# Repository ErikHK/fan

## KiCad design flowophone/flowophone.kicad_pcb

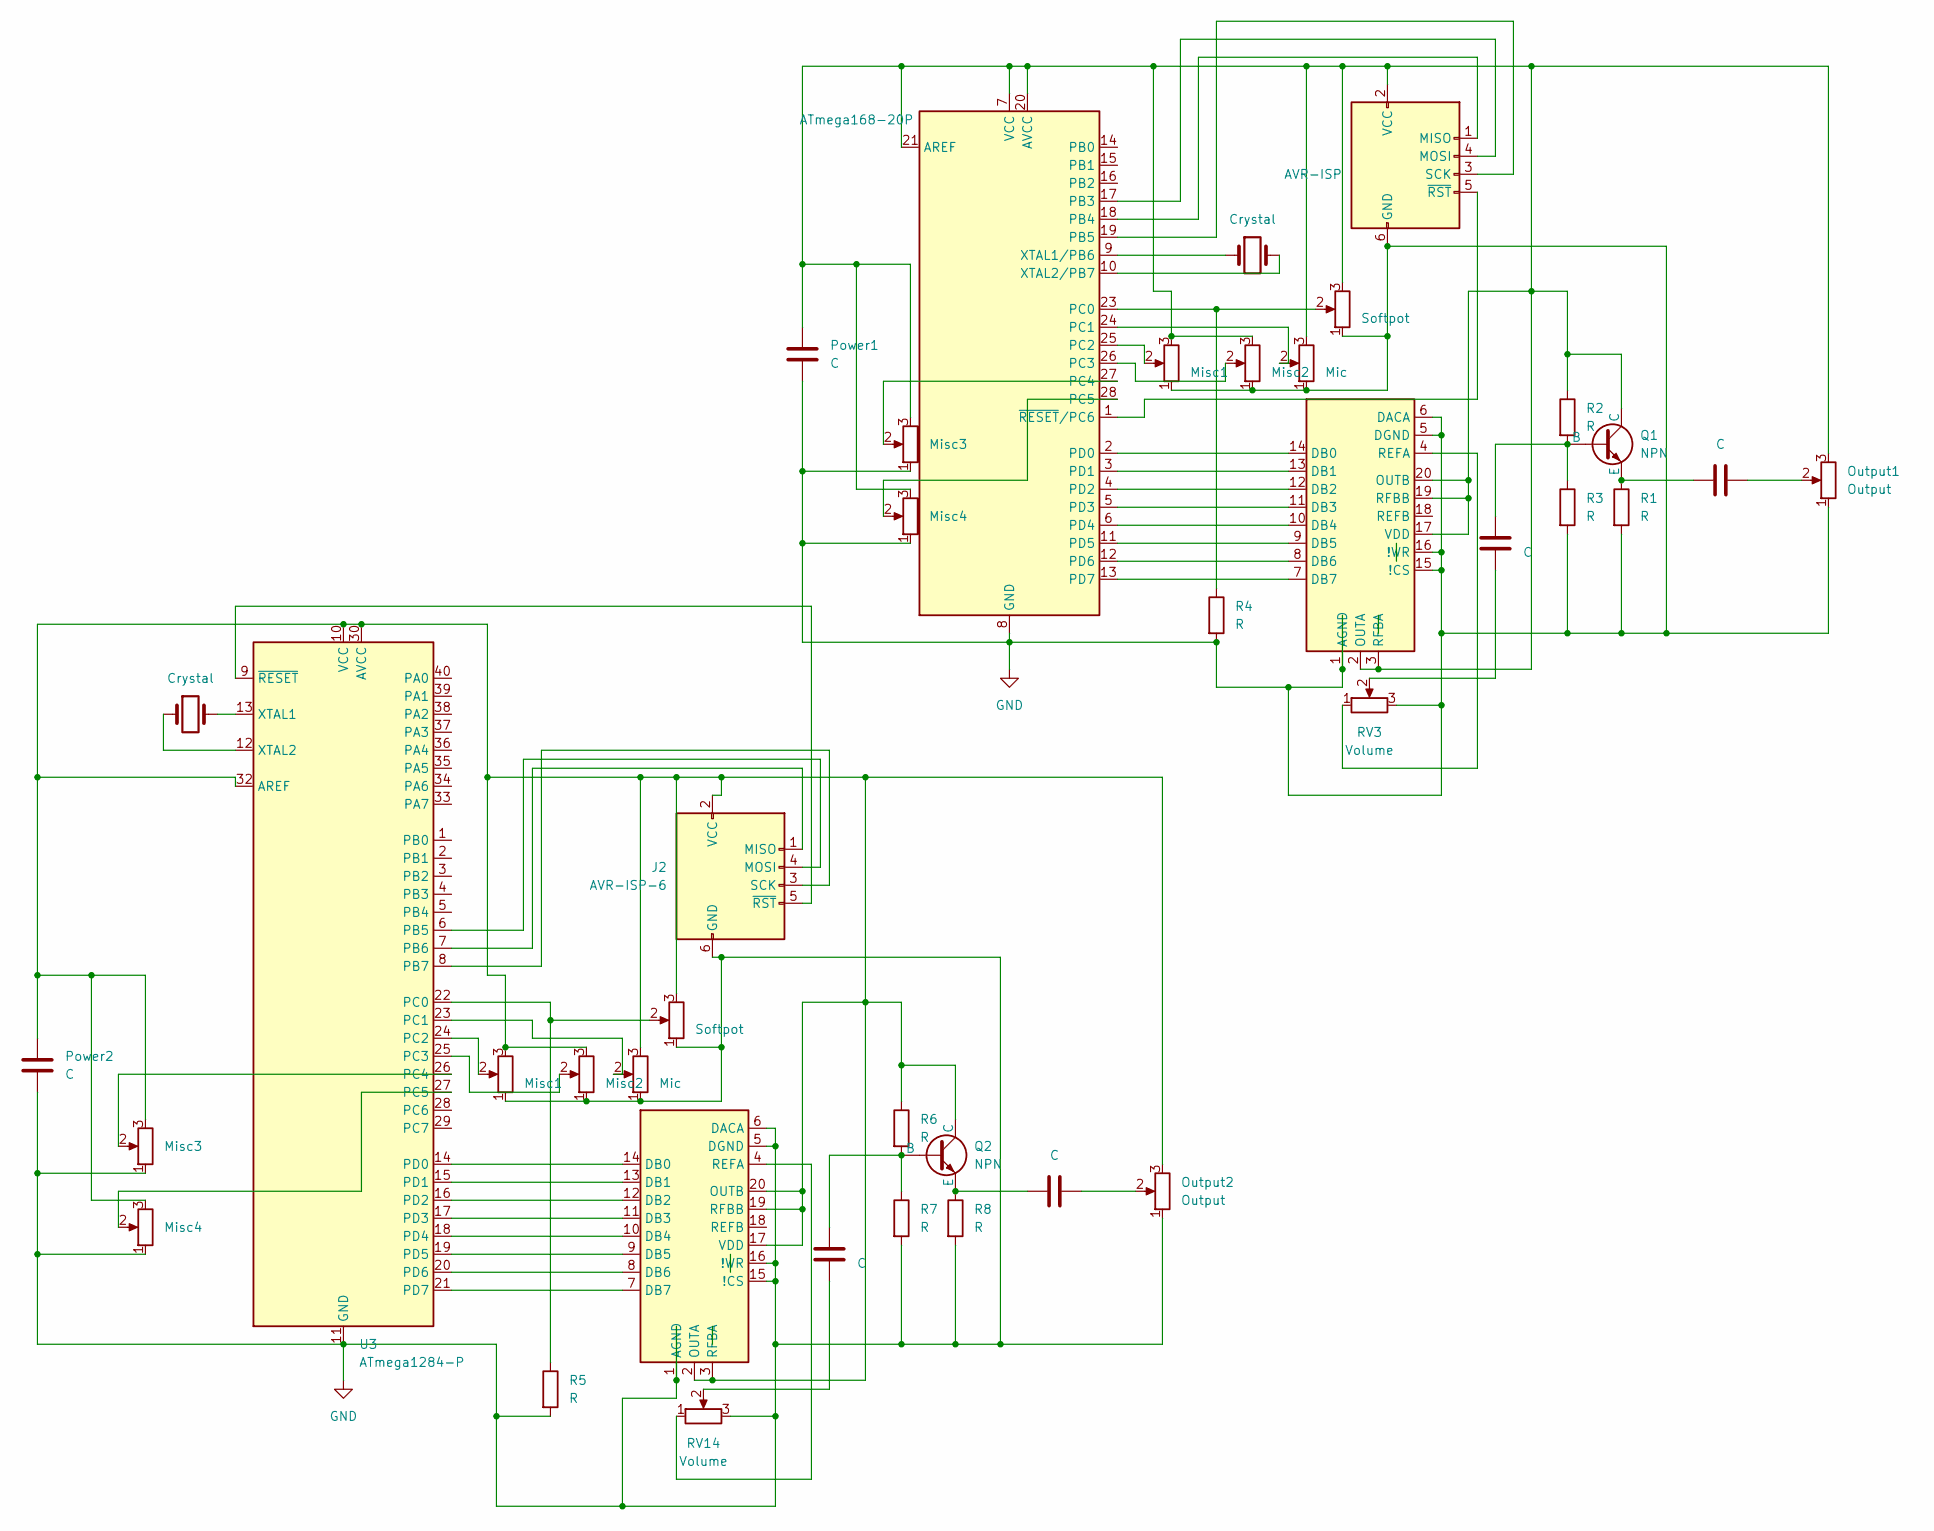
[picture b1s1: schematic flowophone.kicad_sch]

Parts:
C1, C2, C3, C4: C; PinHeader_1x02_P2.54mm_Vertical
J1: AVR-ISP; PinHeader_2x03_P2.54mm_Vertical
J2: AVR-ISP-6; PinHeader_2x03_P2.54mm_Vertical
Output1, Output2: Output; PinHeader_1x03_P2.54mm_Vertical
Power1, Power2: C; PinHeader_1x02_P2.54mm_Vertical
Q1, Q2: NPN; PinHeader_1x03_P2.54mm_Vertical
R1, R2, R3, R4, R5, R6, R7, R8: R; PinHeader_1x02_P2.54mm_Vertical
RV1, RV13: Softpot; PinHeader_1x03_P2.54mm_Vertical
RV2, RV12: Mic; PinHeader_1x03_P2.54mm_Vertical
RV3, RV14: Volume; PinHeader_1x03_P2.54mm_Vertical
RV4, RV10: Misc1; PinHeader_1x03_P2.54mm_Vertical
RV5, RV11: Misc2; PinHeader_1x03_P2.54mm_Vertical
RV6, RV8: Misc3; PinHeader_1x03_P2.54mm_Vertical
RV7, RV9: Misc4; PinHeader_1x03_P2.54mm_Vertical
U1: ATmega168-20P; DIP-28_W7.62mm
U2, U4: DIP-20_W7.62mm
U3: ATmega1284-P; DIP-40_W15.24mm
Y1, Y2: Crystal; PinHeader_1x02_P2.54mm_Vertical

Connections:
GND: J1.6 (GND), J2.6 (GND), Output1.1, Output2.1, Power1.1, Power2.1, R1.2, R3.2, R4.2, R5.2, R7.2, R8.2, RV1.1, RV2.1, RV3.3, RV4.1, RV5.1, RV6.1, RV7.1, RV8.1, RV9.1, RV10.1, RV11.1, RV12.1, RV13.1, RV14.3, U1.8 (GND), U1.22 (GND), U2.1 (AGND), U2.5 (DGND), U2.6 (DACA), U2.15 (!CS), U2.16 (!WR), U3.11 (GND), U3.31 (GND), U4.1 (AGND), U4.5 (DGND), U4.6 (DACA), U4.15 (!CS), U4.16 (!WR)
unnamed: C1.2, RV3.2
unnamed: C2.2, Output1.2
unnamed: C3.2, RV14.2
unnamed: C4.2, Output2.2
unnamed: J1.1 (MISO), U1.18 (PB4)
unnamed: J1.4 (MOSI), U1.17 (PB3)
unnamed: J1.3 (SCK), U1.19 (PB5)
unnamed: J1.2 (VCC), Output1.3, Power1.2, Q1.1 (C), R2.1, RV1.3, RV2.3, RV4.3, RV5.3, RV6.3, RV7.3, U1.7 (VCC), U1.20 (AVCC), U1.21 (AREF), U2.2 (OUTA), U2.3 (RFBA), U2.17 (VDD), U2.19 (RFBB), U2.20 (OUTB)
unnamed: J1.5 (~RST), U1.1 (~RESET/PC6)
unnamed: J2.1 (MISO), U3.7 (PB6)
unnamed: J2.4 (MOSI), U3.6 (PB5)
unnamed: J2.3 (SCK), U3.8 (PB7)
unnamed: J2.2 (VCC), Output2.3, Power2.2, Q2.1 (C), R6.1, RV8.3, RV9.3, RV10.3, RV11.3, RV12.3, RV13.3, U3.10 (VCC), U3.30 (AVCC), U3.32 (AREF), U4.2 (OUTA), U4.3 (RFBA), U4.17 (VDD), U4.19 (RFBB), U4.20 (OUTB)
unnamed: J2.5 (~RST), U3.9 (~RESET)
unnamed: C1.1, Q1.2 (B), R2.2, R3.1
unnamed: C2.1, Q1.3 (E), R1.1
unnamed: C3.1, Q2.2 (B), R6.2, R7.1
unnamed: C4.1, Q2.3 (E), R8.1
unnamed: R4.1, RV1.2, U1.23 (PC0)
unnamed: RV2.2, U1.24 (PC1)
unnamed: RV4.2, U1.25 (PC2)
unnamed: RV5.2, U1.26 (PC3)
unnamed: RV6.2, U1.27 (PC4)
unnamed: RV7.2, U1.28 (PC5)
unnamed: U1.2 (PD0), U2.14 (DB0)
unnamed: U1.3 (PD1), U2.13 (DB1)
unnamed: U1.4 (PD2), U2.12 (DB2)
unnamed: U1.5 (PD3), U2.11 (DB3)
unnamed: U1.6 (PD4), U2.10 (DB4)
unnamed: U1.11 (PD5), U2.9 (DB5)
unnamed: U1.12 (PD6), U2.8 (DB6)
unnamed: U1.13 (PD7), U2.7 (DB7)
unnamed: U1.9 (XTAL1/PB6), Y1.1
unnamed: U1.10 (XTAL2/PB7), Y1.2
unnamed: RV3.1, U2.4 (REFA)
unnamed: R5.1, RV13.2, U3.22 (PC0)
unnamed: RV12.2, U3.23 (PC1)
unnamed: RV10.2, U3.24 (PC2)
unnamed: RV11.2, U3.25 (PC3)
unnamed: RV8.2, U3.26 (PC4)
unnamed: RV9.2, U3.27 (PC5)
unnamed: U3.14 (PD0), U4.14 (DB0)
unnamed: U3.15 (PD1), U4.13 (DB1)
unnamed: U3.16 (PD2), U4.12 (DB2)
unnamed: U3.17 (PD3), U4.11 (DB3)
unnamed: U3.18 (PD4), U4.10 (DB4)
unnamed: U3.19 (PD5), U4.9 (DB5)
unnamed: U3.20 (PD6), U4.8 (DB6)
unnamed: U3.21 (PD7), U4.7 (DB7)
unnamed: U3.13 (XTAL1), Y2.2
unnamed: U3.12 (XTAL2), Y2.1
unnamed: RV14.1, U4.4 (REFA)

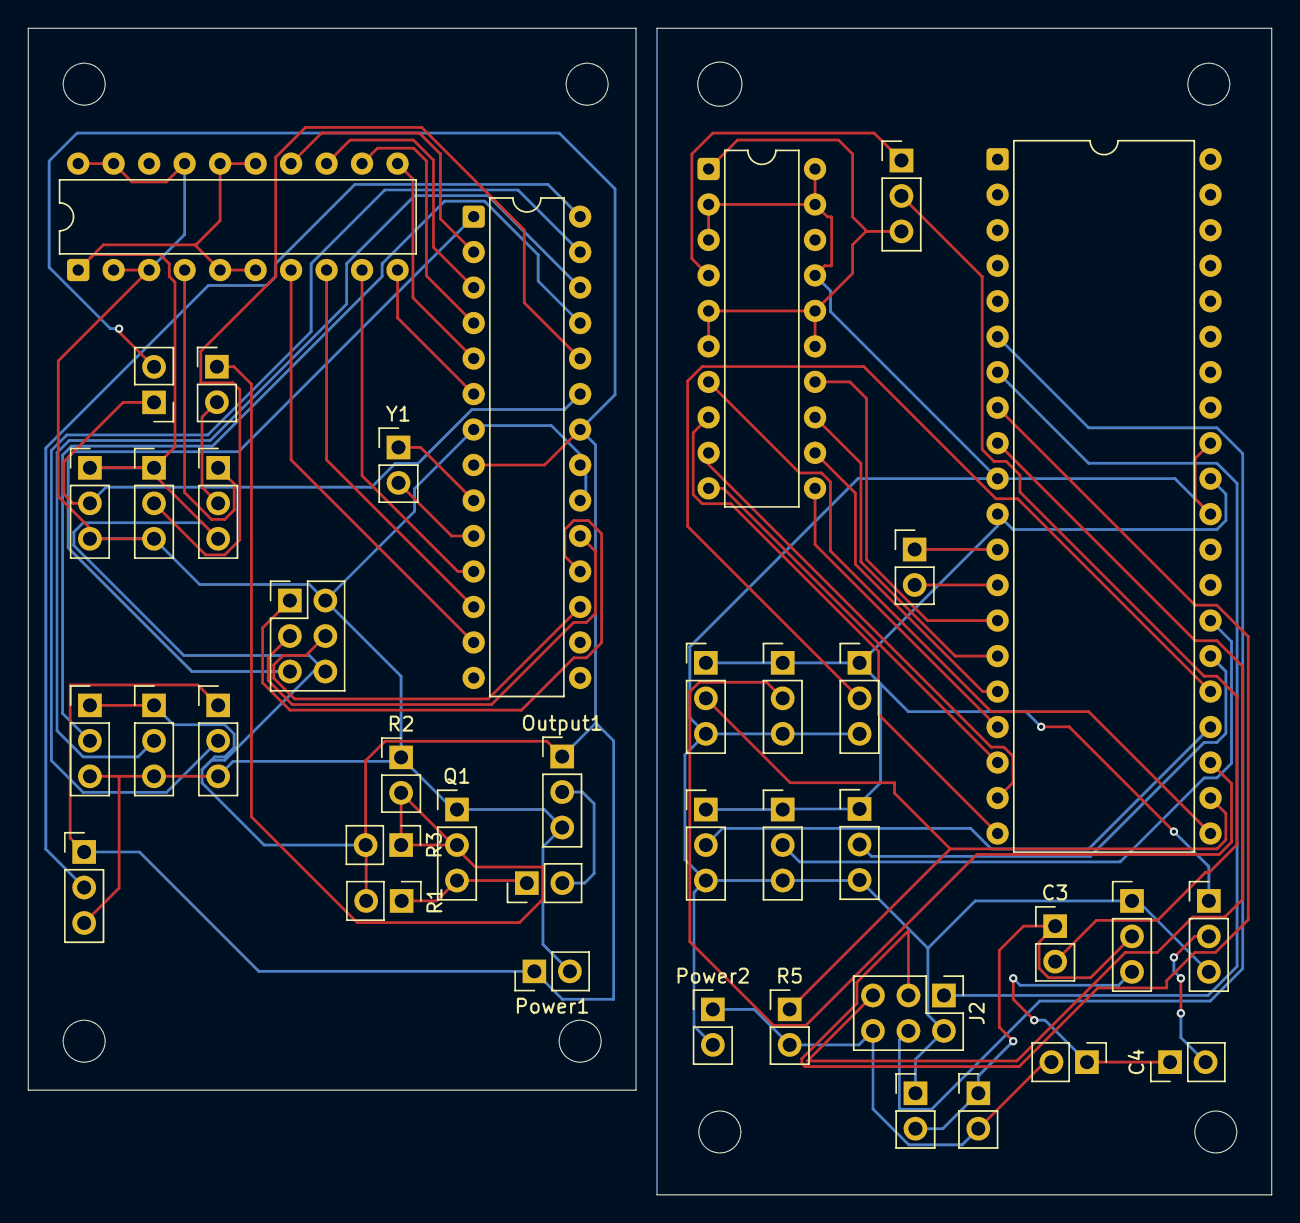
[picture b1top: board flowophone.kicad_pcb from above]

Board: 2 copper layers, 89.0 x 83.5 mm, 40 parts (0 on the bottom side), 53 nets.

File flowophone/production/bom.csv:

Designator,Footprint,Quantity,Value,LCSC Part #
"C1, C2, C3, C4, POWER1, POWER2",PinHeader_1x02_P2.54mm_Vertical,6,C,
J1,PinHeader_2x03_P2.54mm_Vertical,1,AVR-ISP,
J2,PinHeader_2x03_P2.54mm_Vertical,1,AVR-ISP-6,
"OUTPUT1, OUTPUT2",PinHeader_1x03_P2.54mm_Vertical,2,Output,
"Q1, Q2",PinHeader_1x03_P2.54mm_Vertical,2,NPN,
"R1, R2, R3, R4, R5, R6, R7, R8",PinHeader_1x02_P2.54mm_Vertical,8,R,
"RV1, RV13",PinHeader_1x03_P2.54mm_Vertical,2,Softpot,
"RV10, RV4",PinHeader_1x03_P2.54mm_Vertical,2,Misc1,
"RV11, RV5",PinHeader_1x03_P2.54mm_Vertical,2,Misc2,
"RV12, RV2",PinHeader_1x03_P2.54mm_Vertical,2,Mic,
"RV14, RV3",PinHeader_1x03_P2.54mm_Vertical,2,Volume,
"RV6, RV8",PinHeader_1x03_P2.54mm_Vertical,2,Misc3,
"RV7, RV9",PinHeader_1x03_P2.54mm_Vertical,2,Misc4,
U1,DIP-28_W7.62mm,1,ATmega168-20P,
"U2, U4",DIP-20_W7.62mm,2,~,
U3,DIP-40_W15.24mm,1,ATmega1284-P,
"Y1, Y2",PinHeader_1x02_P2.54mm_Vertical,2,Crystal,

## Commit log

2026-02-03 adjusted to atmega1284p
2026-02-09 adc is now interrupt driven
2026-02-12 non-functioning code... whyyy
2026-02-12 works again...
2026-02-13 omg moved code lol....
2026-02-13 inbefore major rehaul
2026-02-21 fixed tremolo
2026-04-12 added lots
2026-04-12 cleaned up code a looot
2026-04-13 continuous adc woop
2026-04-13 continuous adc and more tasks, also 1000 hz tick
2026-04-13 removed a bunch of log files...
2026-04-19 drum mode almost
